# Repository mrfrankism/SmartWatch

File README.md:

## Welcome to my Smart Watch Project

This Project was started May 2017 and is still being worked on.
For more detailed Information check out the [wiki](https://github.com/mrfrankism/SmartWatch/wiki)

### Current Status:
* Currently the watch has undergone 2 prototypes.
* 2nd Prototype spin:

* The 2nd prototype was fabbed with the incorrecct package for the atmega328, so the 3rd spin will fix this issue without adding new       features for now
* Case for the watch is being designed to be 3D printed

### Initial goals for this project are:
* Working screen
* Actual simple watch functionality
* Computer to watch communication (SPI, UART)
* Bluetooth connectivity to phone 
* Notifications
* Probably going to need to make an app for full bluetooth-notification functionality
* Decent battery life (6 hours)
* Ability to charge easily from usb

### Extra goals:
* SOS signal - Being able to send a text with GPS coordinates to emergency contact, using only the watch 
* LTE connectivity
* Accelerometer
* Gyro
* Wifi?
* GPS

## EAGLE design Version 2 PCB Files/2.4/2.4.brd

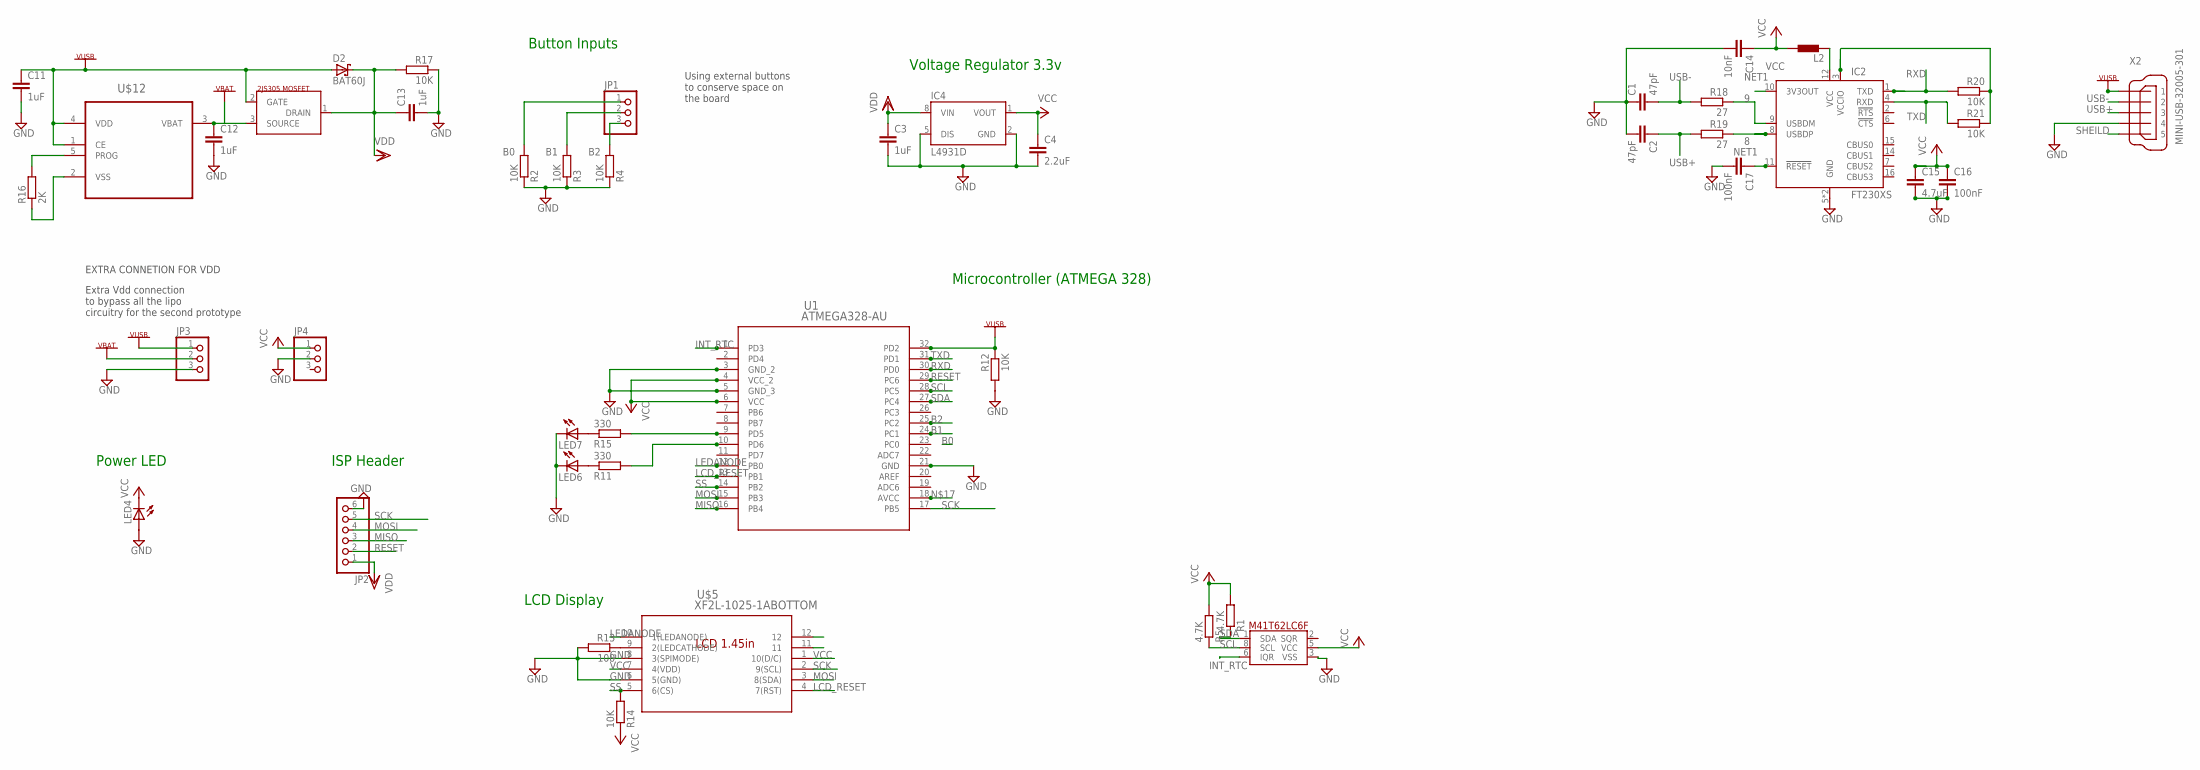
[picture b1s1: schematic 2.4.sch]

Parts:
C1, C2: 47pF; C0603K
C3, C11, C12, C13: 1uF; C0603K
C4: 2.2uF; C0603K
C14: 10nF; C0603K
C15: 4.7uF; C0603K
C16, C17: 100nF; C0603K
D2: BAT60J; SOD323_ST
IC2: FT230XS; SSOP16
IC4: L4931D; SO08
JP1, JP3, JP4: PINHD-1X3CB; 1X03-CLEANBIG
JP2: PINHD-1X6B; 1X06-BIG
L2: BLM15HB221SN1; 0402
LED4, LED6, LED7: LEDSMT1206; 1206
R1, R5: 4.7K; R0603
R2, R3, R4, R12, R14, R17, R20, R21: 10K; R0603
R11, R15: 330; R0603
R13: 100; R0603
R16: 2K; R0603
R18, R19: 27; R0603
U1: ATMEGA328-AU; 32A
U$1: M41T62LC6F; LCC-8
U$5: XF2L-1025-1ABOTTOM; CON10_1X10_DBR_XF2L
U$12: MCP73812T-420I/OT; SOT95P270X145-5N
U$13: 2JS305; SOT346-R
X2: MINI-USB-32005-301; 32005-301

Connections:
8: IC2.8 (USBDP), R19.1
9: IC2.9 (USBDM), R18.1
B0: JP1.1, R2.2
B1: JP1.2, R3.2
B2: JP1.3, R4.2
GND: C1.1, C2.2, C3.2, C4.2, C11.2, C12.2, C13.2, C14.2, C15.2, C16.2, C17.2, IC2.5 (GND), IC2.13 (GND), IC4.2 (GND), IC4.5 (DIS), JP2.6, JP3.3, JP4.2, LED4.A, LED6.C, LED7.C, R2.1, R3.1, R4.1, R12.2, R13.2, R17.1, U$1.3 (VSS), U$5.6 (5(GND)), U$5.8 (3(SPIMODE)), X2.4
INT_RTC: U$1.6 (IQR)
LCD_RESET: U$5.4 (7(RST))
LEDANODE: U$5.10 (1(LEDANODE))
MISO: JP2.3
MOSI: JP2.4, U$5.3 (8(SDA))
unnamed: R13.1, U$5.9 (2(LEDCATHODE))
unnamed: IC2.12 (VCC), L2.1
unnamed: R16.2, U$12.5 (PROG)
unnamed: R16.1, U$12.2 (VSS)
unnamed: LED6.A, R11.1
unnamed: LED7.A, R15.1
NET1: C17.1, IC2.3 (VCCIO), IC2.10 (3V3OUT), IC2.11 (!RESET), R20.1, R21.1
RESET: JP2.2
RXD: IC2.1 (TXD), R20.2
SCK: JP2.5, U$5.2 (9(SCL))
SCL: R5.1, U$1.8 (SCL)
SDA: R1.1, U$1.1 (SDA)
SHEILD: X2.5
SS: R14.2, U$5.5 (6(CS))
TXD: IC2.4 (RXD), R21.2
USB+: C2.1, R19.2, X2.3
USB-: C1.2, R18.2, X2.2
VBAT: C12.1, JP3.2, U$12.3 (VBAT), U$13.3 (SOURCE)
VCC: C4.1, C14.1, C15.1, C16.1, IC4.1 (VOUT), JP4.1, L2.2, LED4.C, R1.2, R5.2, R14.1, U$1.5 (VCC), U$5.1 (10(D/C)), U$5.7 (4(VDD))
VDD: C3.1, C13.1, D2.C, IC4.8 (VIN), JP2.1, R17.2, U$13.1 (DRAIN)
VUSB: C11.1, D2.A, JP3.1, R12.1, U$12.1 (CE), U$12.4 (VDD), U$13.2 (GATE), X2.1

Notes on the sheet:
Button Inputs
Voltage Regulator 3.3v
Power LED
EXTRA CONNETION FOR VDD
Extra Vdd connection to bypass all the lipo circuitry for the second prototype
ISP Header
Microcontroller (ATMEGA 328)
LCD Display
Using external buttons to conserve space on the board

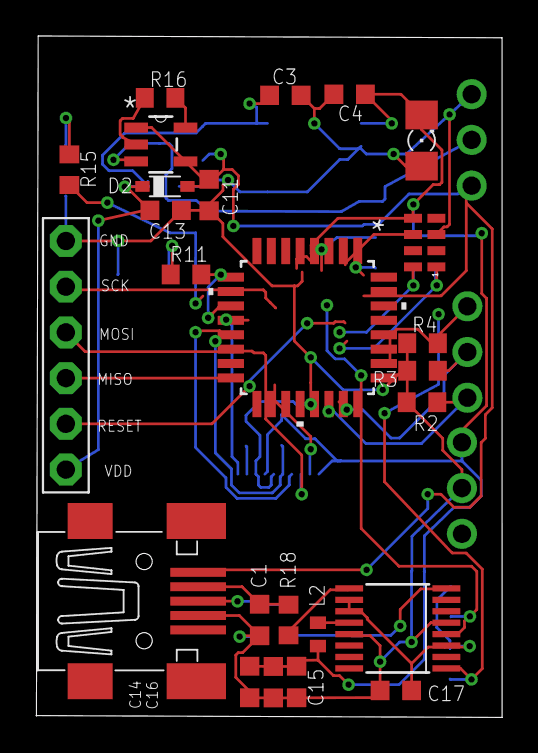
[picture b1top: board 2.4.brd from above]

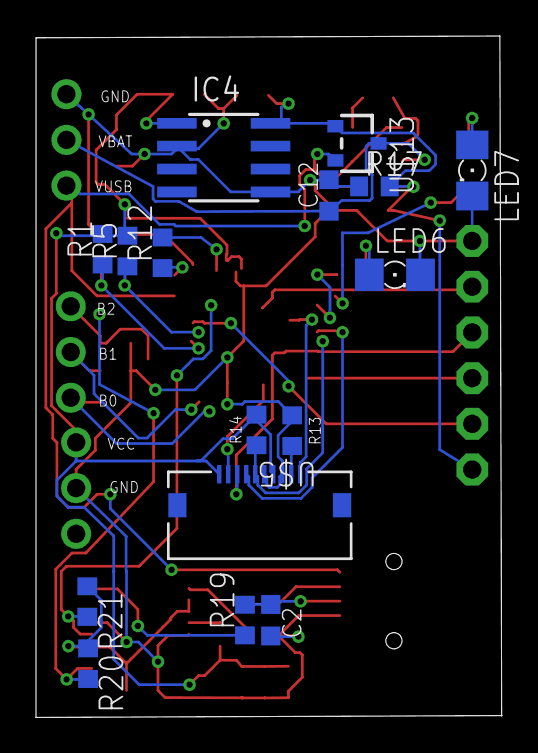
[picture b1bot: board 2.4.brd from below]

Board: 2 copper layers, 25.9 x 37.9 mm, 44 parts (16 on the bottom side), 26 nets.

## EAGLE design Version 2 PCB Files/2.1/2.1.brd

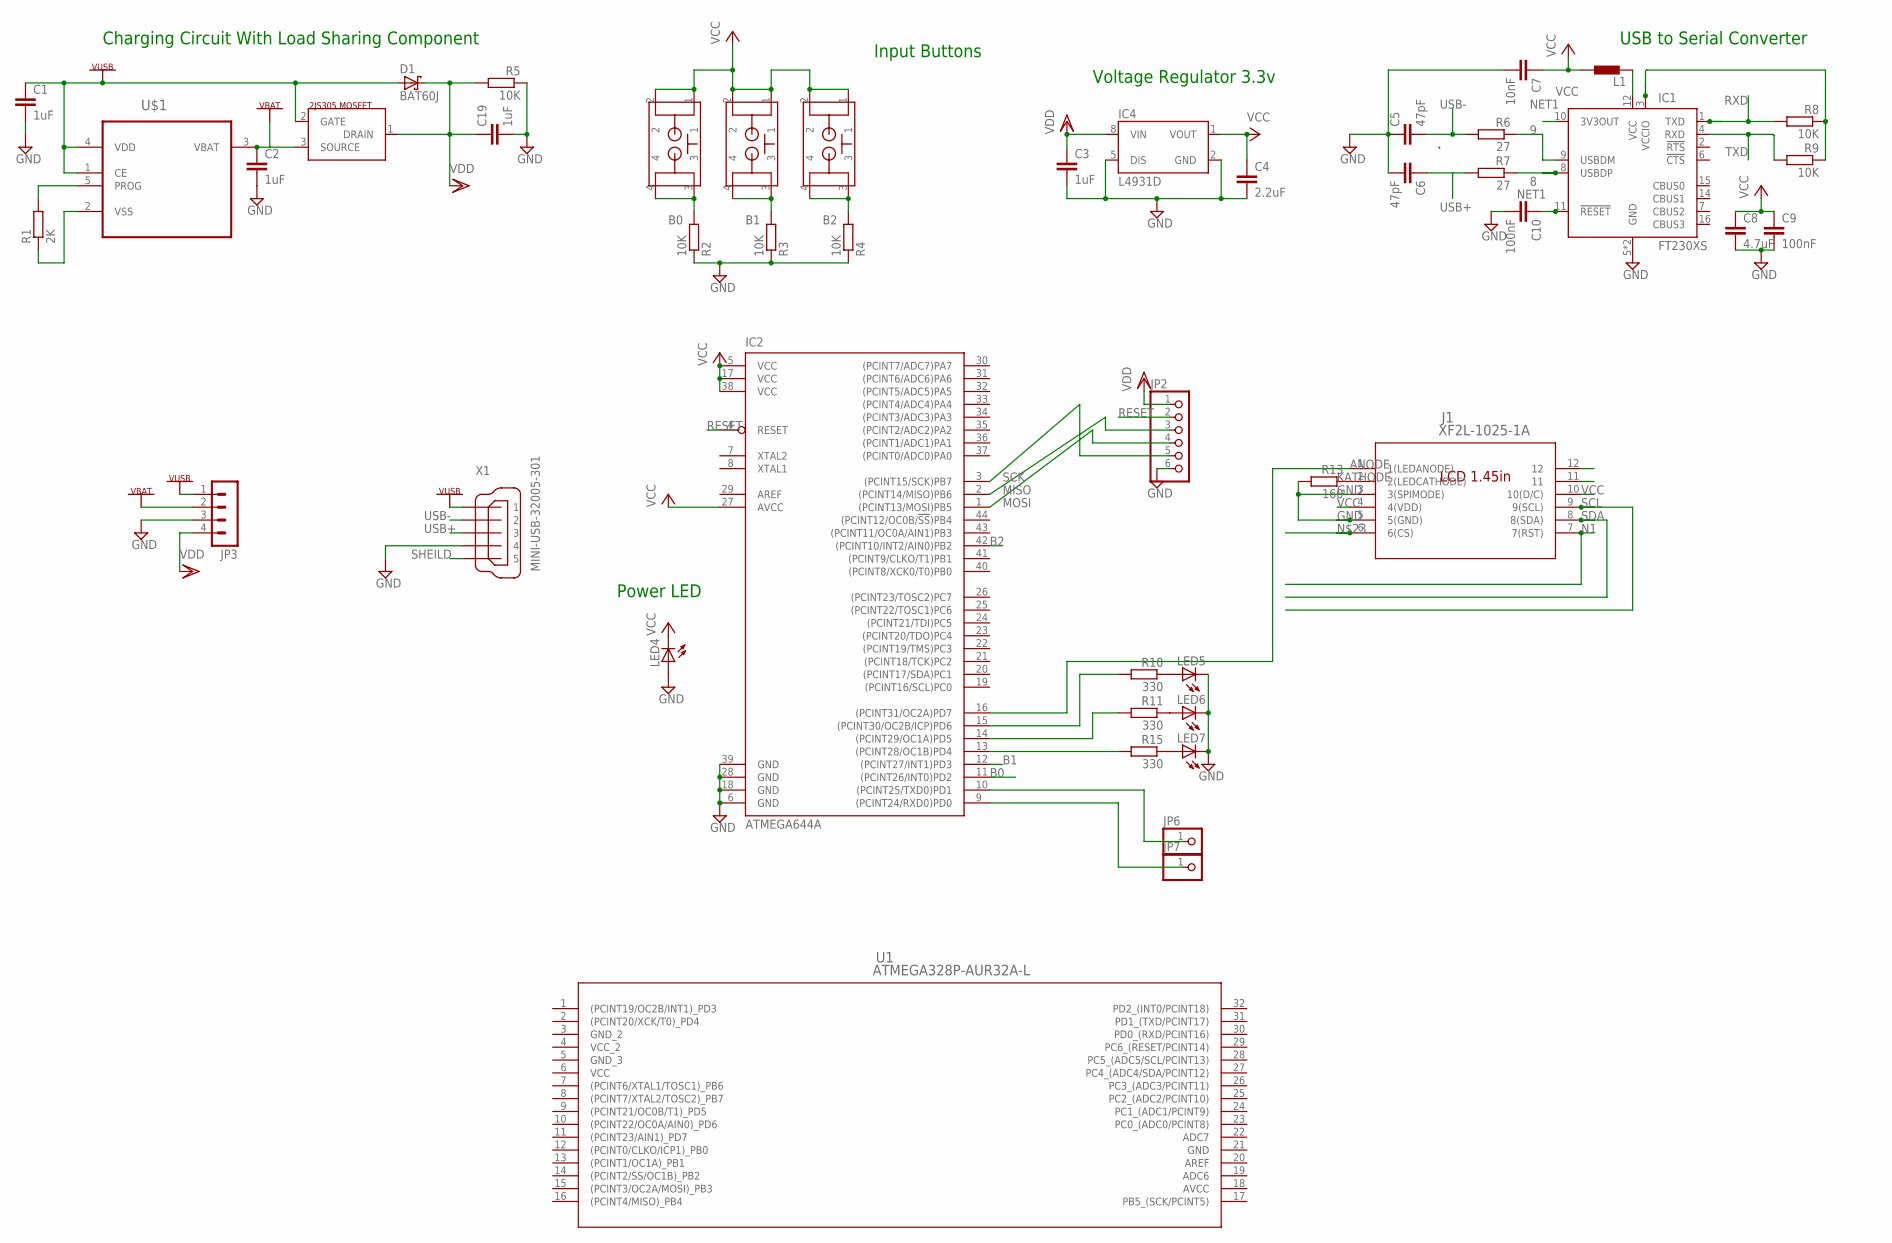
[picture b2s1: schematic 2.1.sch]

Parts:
C1, C2, C3, C19: 1uF; C0603K
C4: 2.2uF; C0603K
C5, C6: 47pF; C0603K
C7: 10nF; C0603K
C8: 4.7uF; C0603K
C9, C10: 100nF; C0603K
D1: BAT60J; SOD323_ST
IC1: FT230XS; SSOP16
IC2: ATMEGA644A; TQFP44
IC4: L4931D; SO08
J1: XF2L-1025-1A; CON10_1X10_DBR_XF2L
JP2: PINHD-1X6B; 1X06-BIG
JP3: MA04-1
JP6, JP7: PINHD-1X1; 1X01
L1: BLM15HB221SN1; 0402
LED4, LED5, LED6, LED7: LEDSMT1206; 1206
R1: 2K; R0603
R2, R3, R4, R5, R8, R9: 10K; R0603
R6, R7: 27; R0603
R10, R11, R15: 330; R0603
R13: 160; R0603
U1: ATMEGA328P-AUR32A-L; 32A-L
U$1: MCP73812T-420I/OT; SOT95P270X145-5N
U$2: 2JS305; SOT346-R
U$3, U$4, U$11: TL3315NF100Q; TL3315NF100Q-PACKAGE
X1: MINI-USB-32005-301; 32005-301

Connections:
8: IC1.8 (USBDP), R7.1
9: IC1.9 (USBDM), R6.1
ANODE: IC2.16 ((PCINT31/OC2A)PD7), J1.1 (1(LEDANODE))
AVCC: U1.18 (AVCC)
B0: IC2.11 ((PCINT26/INT0)PD2), R2.2, U$3.3, U$3.4
B1: IC2.12 ((PCINT27/INT1)PD3), R3.2, U$4.3, U$4.4
B2: IC2.42 ((PCINT10/INT2/AIN0)PB2), R4.2, U$11.3, U$11.4
FTDI_VCC: IC1.12 (VCC), L1.1
GND: C1.2, C2.2, C3.2, C4.2, C5.1, C6.2, C7.2, C8.2, C9.2, C10.2, C19.2, IC1.5 (GND), IC1.13 (GND), IC2.6 (GND), IC2.18 (GND), IC2.28 (GND), IC2.39 (GND), IC4.2 (GND), IC4.5 (DIS), J1.3 (3(SPIMODE)), J1.5 (5(GND)), JP2.6, JP3.3, LED4.A, LED5.C, LED6.C, LED7.C, R2.1, R3.1, R4.1, R5.1, R13.2, U1.21 (GND), X1.4
GND_2: U1.3 (GND_2)
GND_3: U1.5 (GND_3)
KATHODE: J1.2 (2(LEDCATHODE)), R13.1
MISO: IC2.2 ((PCINT14/MISO)PB6), JP2.3
MOSI: IC2.1 ((PCINT13/MOSI)PB5), JP2.4
N1: J1.7 (7(RST))
unnamed: R1.2, U$1.5 (PROG)
unnamed: R1.1, U$1.2 (VSS)
unnamed: LED5.A, R10.1
unnamed: LED6.A, R11.1
unnamed: LED7.A, R15.1
unnamed: IC2.13 ((PCINT28/OC1B)PD4), R15.2
unnamed: IC2.14 ((PCINT29/OC1A)PD5), R11.2
unnamed: IC2.15 ((PCINT30/OC2B/ICP)PD6), R10.2
unnamed: IC2.10 ((PCINT25/TXD0)PD1), JP6.1
NET1: C10.1, IC1.3 (VCCIO), IC1.10 (3V3OUT), IC1.11 (!RESET), R8.1, R9.1
RESET: IC2.4 (RESET), JP2.2
RXD: IC1.1 (TXD), R8.2
RXD1: IC2.9 ((PCINT24/RXD0)PD0), JP7.1
SCK: IC2.3 ((PCINT15/SCK)PB7), JP2.5
SCL: J1.9 (9(SCL))
SDA: J1.8 (8(SDA))
SHEILD: X1.5
TXD: IC1.4 (RXD), R9.2
USB+: C6.1, R7.2, X1.3
USB-: C5.2, R6.2, X1.2
VBAT: C2.1, JP3.2, U$1.3 (VBAT), U$2.3 (SOURCE)
VCC: C4.1, C7.1, C8.1, C9.1, IC2.5 (VCC), IC2.17 (VCC), IC2.27 (AVCC), IC2.38 (VCC), IC4.1 (VOUT), J1.4 (4(VDD)), J1.10 (10(D/C)), L1.2, LED4.C, U1.6 (VCC), U$3.1, U$3.2, U$4.1, U$4.2, U$11.1, U$11.2
VCC_2: U1.4 (VCC_2)
VDD: C3.1, C19.1, D1.C, IC4.8 (VIN), JP2.1, JP3.4, R5.2, U$2.1 (DRAIN)
VUSB: C1.1, D1.A, JP3.1, U$1.1 (CE), U$1.4 (VDD), U$2.2 (GATE), X1.1

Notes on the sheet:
Charging Circuit With Load Sharing Component
Input Buttons
Voltage Regulator 3.3v
USB to Serial Converter
Power LED

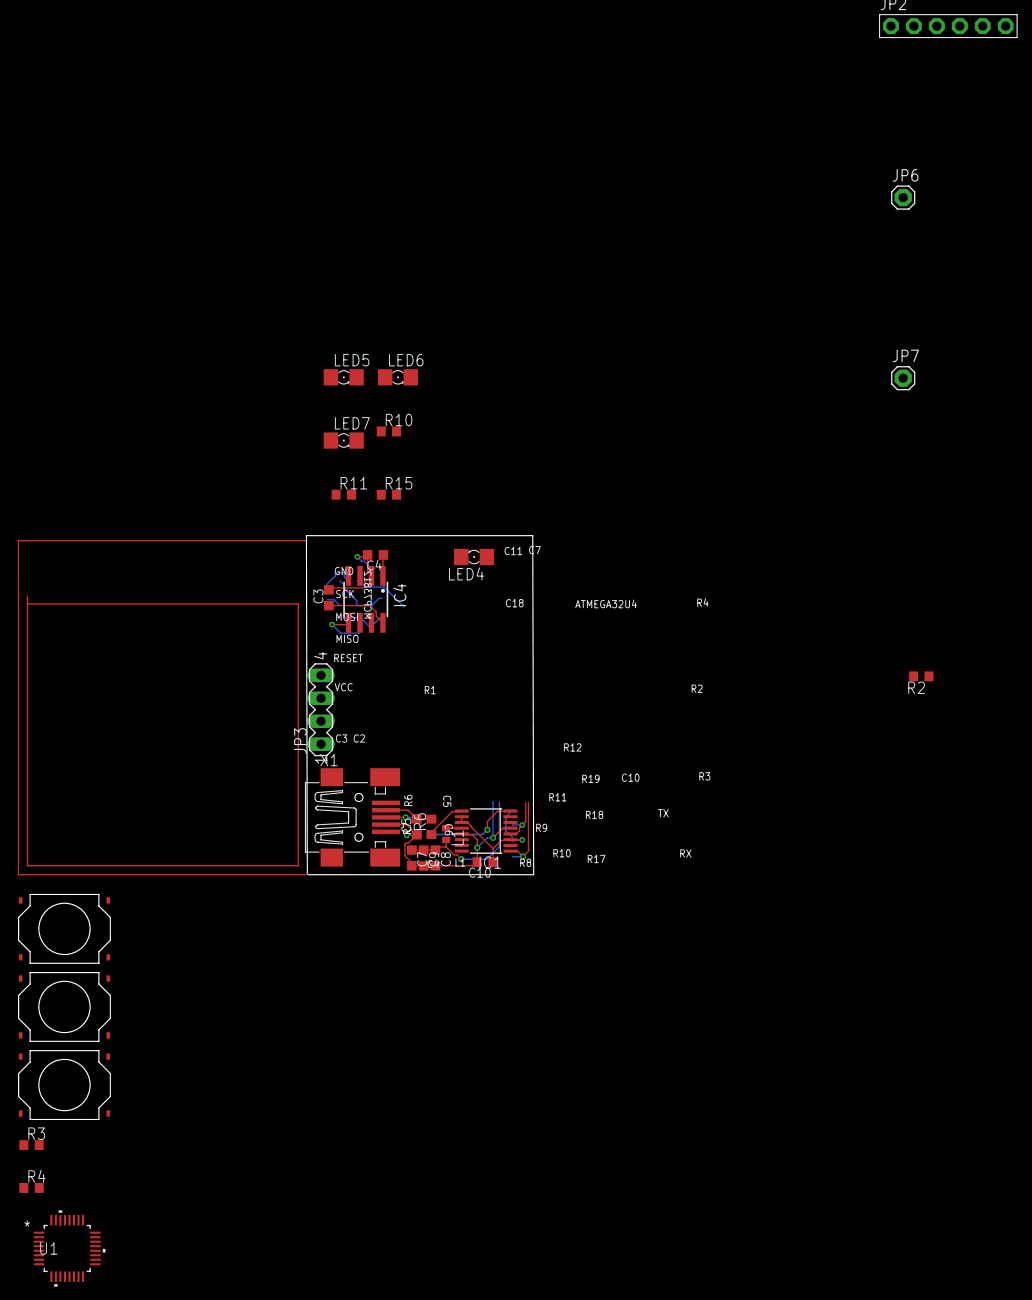
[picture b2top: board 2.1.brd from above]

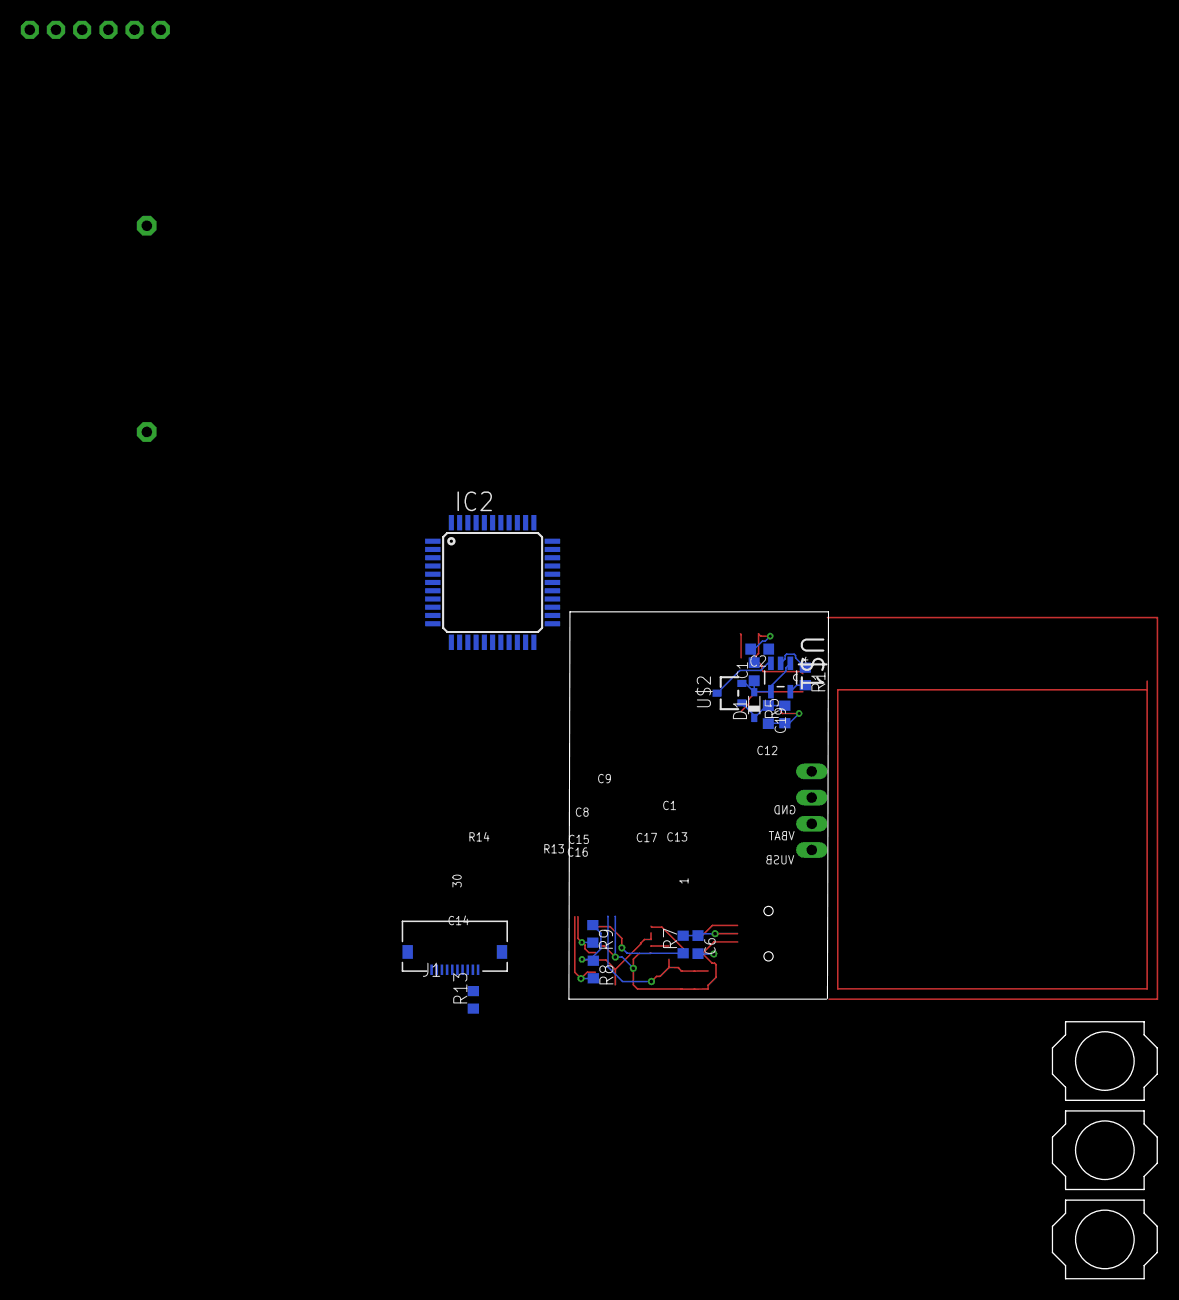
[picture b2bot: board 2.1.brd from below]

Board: 2 copper layers, 45 parts (15 on the bottom side), 32 nets.

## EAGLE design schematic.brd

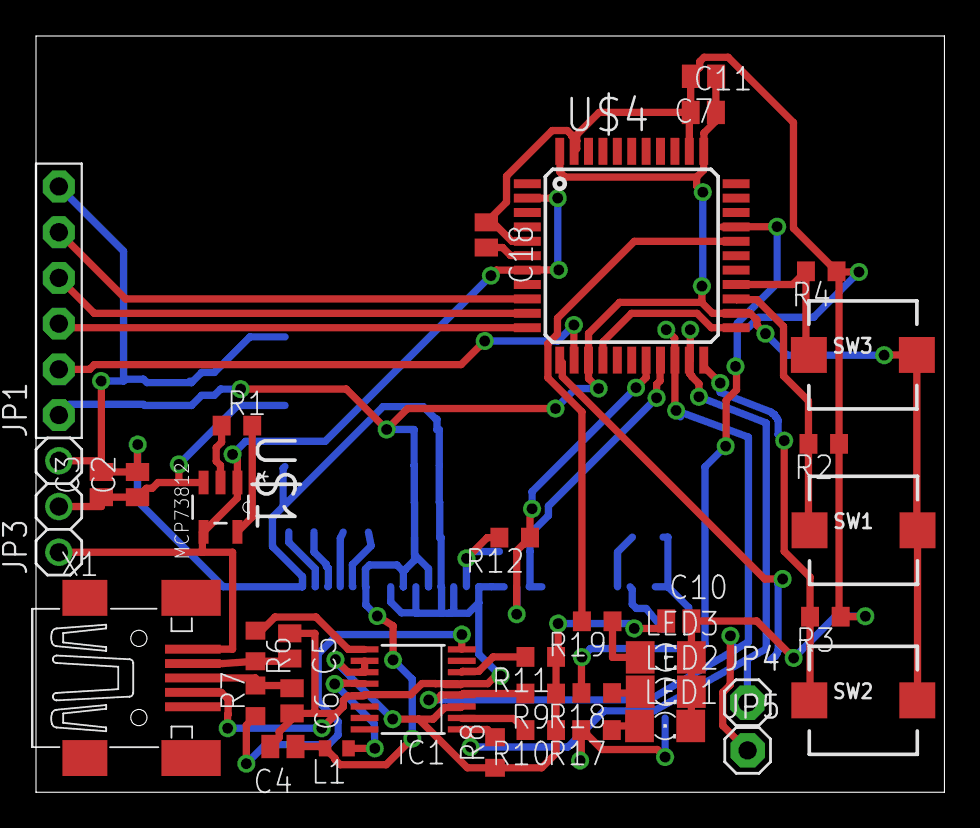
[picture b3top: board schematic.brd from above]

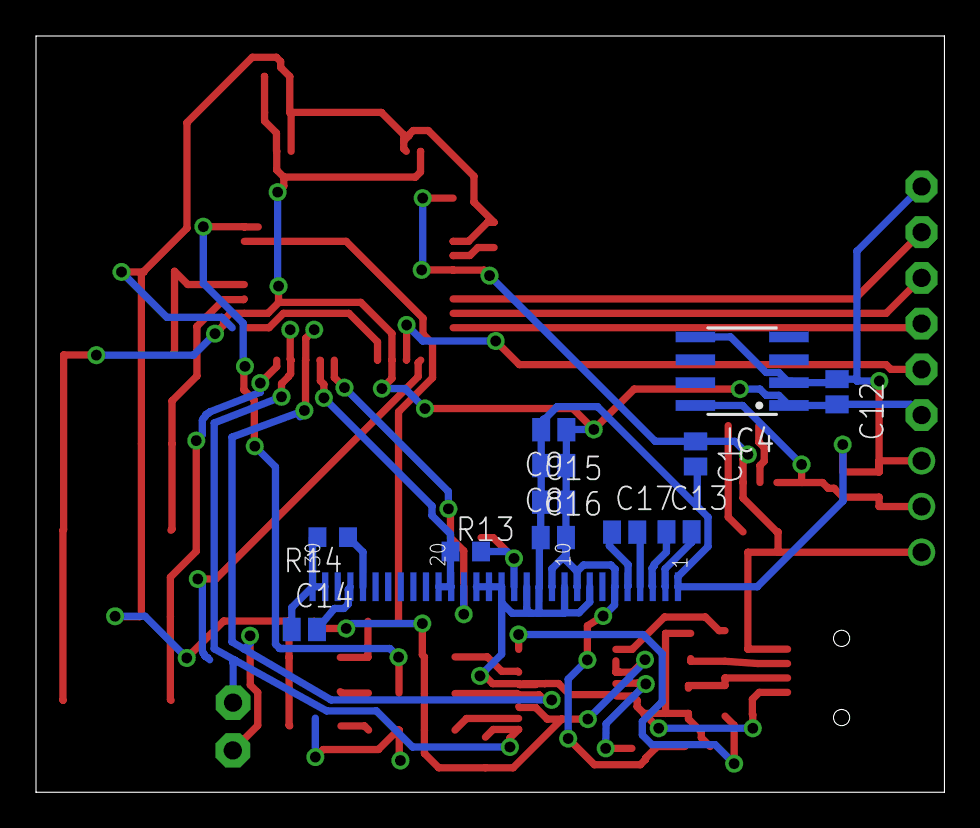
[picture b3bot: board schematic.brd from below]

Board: 2 copper layers, 50.5 x 42.0 mm, 51 parts (13 on the bottom side), 39 nets.

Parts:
C1, C2, C3, C12, C13, C17, C18: 1uF; C0504
C4, C14, C15: 2.2uF; C0504
C5, C6: 47pF; C0504
C7: 10nF; C0504
C8: 4.7uF; C0504
C9, C10: 100nF; C0504
C11: .1uf; C0504
C16: .1uF; C0504
IC1: FT230XS; SSOP16
IC4: L4931D; SO08
JP1: 1X06-BIG
JP3: 1X03
JP4, JP5: 1X01
L1: 0402
LED1, LED2, LED3: 1206
R1, R12, R13: 2K; R0603
R2, R3, R4, R8, R9, R10, R11: 10K; R0603
R6, R7: 27; R0603
R14: 390K; R0603
R17, R18, R19: 330; R0603
SW1, SW2, SW3: PUSHBUTTON_SMD_SJ
U$1: SOT95P270X145-5N
U$3: UG-2864HSWEG01; 1X30-0.7MM
U$4: ATMEGA32U4-AU; TQFP44
X1: MINI-USB-32005-301; 32005-301

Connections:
8: IC1.8, R7.1
9: IC1.9, R6.1
B0: R2.2, SW1.P$2, U$4.25
B1: R3.2, SW2.P$2, U$4.22
B2: R4.2, SW3.P$2, U$4.26
FTDI_VCC: IC1.12, L1.1
GND: C1.2, C2.2, C3.2, C4.2, C5.1, C6.2, C7.2, C8.2, C9.2, C10.2, C11.1, C12.1, C14.1, C15.1, C16.1, C18.1, IC1.5, IC1.13, IC4.2, IC4.5, JP1.6, JP3.3, LED1.C, LED2.C, LED3.C, R2.1, R3.1, R4.1, R14.2, U$3.1, U$3.8, U$3.10, U$3.12, U$3.13, U$3.15, U$3.16, U$3.17, U$3.29, U$3.30, U$4.5, U$4.15, U$4.23, U$4.35, U$4.43, X1.4
MISO: JP1.3, U$4.11
MOSI: JP1.4, U$4.10
unnamed: R1.2, U$1.5
unnamed: R1.1, U$1.2
unnamed: C14.2, U$3.27
unnamed: IC1.2, R10.2
unnamed: C13.2, U$3.2
unnamed: IC1.6, R11.2
unnamed: R14.1, U$3.26
unnamed: C13.1, U$3.3
unnamed: C17.2, U$3.4
unnamed: C17.1, U$3.5
unnamed: C18.2, U$4.6
unnamed: LED1.A, R17.1
unnamed: LED2.A, R18.1
unnamed: LED3.A, R19.1
unnamed: R19.2, U$4.29
unnamed: R18.2, U$4.30
unnamed: R17.2, U$4.12
NET1: C10.1, IC1.3, IC1.10, IC1.11, R8.1, R9.1, R10.1, R11.1
OLED_SCL: R12.1, U$3.18, U$4.18
OLED_SDA: R13.1, U$3.19, U$3.20, U$4.19
OLED_VDD: R12.2, R13.2
RESET: JP1.2, U$4.13
RXD: IC1.4, JP5.1, R9.2, U$4.20
SCK: JP1.5, U$4.9
TXD: IC1.1, JP4.1, R8.2, U$4.21
USB+: C6.1, R7.2, X1.3
USB-: C5.2, R6.2, X1.2
VBAT+: C2.1, C3.1, IC4.8, JP3.2, U$1.3
VCC: C4.1, C7.1, C8.1, C9.1, C11.2, C12.2, C15.2, C16.2, IC4.1, JP1.1, L1.2, SW1.P$1, SW2.P$1, SW3.P$1, U$3.6, U$3.9, U$3.11, U$3.14, U$3.28, U$4.14, U$4.24, U$4.34, U$4.44
VUSB: C1.1, JP3.1, U$1.1, U$1.4, U$4.2, U$4.7, X1.1

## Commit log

2017-05-16 First Push
2017-05-17 saving to git
2017-05-17 saving
2017-05-21 Finished layout V1
2017-05-21 Checked and fixed with OSH Park DRC
2017-05-21 Added Power LED, passed DRC
2017-05-22 Added a version 1 folder, all upcomming work will be in a version 2 folder for the next prototype run
2017-06-02 Changing up file structure
2017-06-03 Started V2 Schematic, need to put in smaller buttons, etc
2017-07-26 Added a way to bypass LIPO charging circuitry which wont be ready for the next prototype
2017-08-07 Need to layout board and send to fab
    Switched to the atmega 328 for simplicity and size, well see what happens, should add an rtc to the board, or a spi header to test the i2c with
2017-08-17 Version 2.2 Is finished!
    Sent the board to the fab waiting for it.
2017-08-17 Set theme jekyll-theme-slate
2017-08-18 Working on Presentation and Organizing
2017-08-18 Updating Readme with wiki info
2017-08-22 Updating Current Status
2017-10-15 Changed the Atmega 328 to the correct package size
2017-10-16 Routed the board with the new Atmega package on it
